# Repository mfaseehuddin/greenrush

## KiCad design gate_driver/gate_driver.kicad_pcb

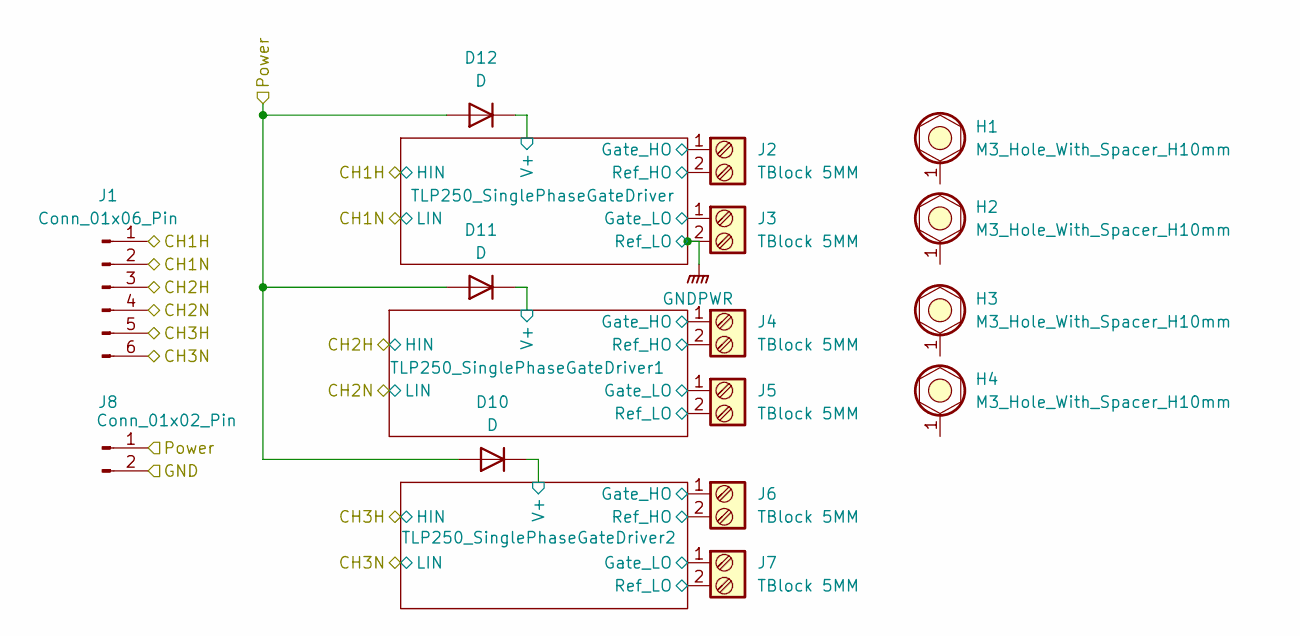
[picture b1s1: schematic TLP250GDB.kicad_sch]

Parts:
D10, D11, D12: D; D_5W_P10.16mm_Horizontal
H1, H2, H3, H4: M3_Hole_With_Spacer_H10mm; MountingHole_3.2mm_With_Spacer_H10mm
J1: Conn_01x06_Pin; PinHeader_1x06_P2.54mm_Vertical
J2, J3, J4, J5, J6, J7: TBlock 5MM; TerminalBlock_Phoenix_PT-1,5-2-5.0-H_1x02_P5.00mm_Horizontal
J8: Conn_01x02_Pin; PinHeader_1x02_P2.54mm_Vertical

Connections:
/Gate Driver Board/CH1H: J1.1; also elsewhere on the board
/Gate Driver Board/CH1N: J1.2; also elsewhere on the board
/Gate Driver Board/CH2H: J1.3; also elsewhere on the board
/Gate Driver Board/CH2N: J1.4; also elsewhere on the board
/Gate Driver Board/CH3H: J1.5; also elsewhere on the board
/Gate Driver Board/CH3N: J1.6; also elsewhere on the board
/Gate Driver Board/TLP250_SinglePhaseGateDriver1/Gate_HO: J4.1; also elsewhere on the board
/Gate Driver Board/TLP250_SinglePhaseGateDriver1/Gate_LO: J5.1; also elsewhere on the board
/Gate Driver Board/TLP250_SinglePhaseGateDriver1/Ref_HO: J4.2; also elsewhere on the board
/Gate Driver Board/TLP250_SinglePhaseGateDriver1/Ref_LO: J5.2; also elsewhere on the board
/Gate Driver Board/TLP250_SinglePhaseGateDriver1/V+: D11.1 (K); also elsewhere on the board
/Gate Driver Board/TLP250_SinglePhaseGateDriver2/Gate_HO: J6.1; also elsewhere on the board
/Gate Driver Board/TLP250_SinglePhaseGateDriver2/Gate_LO: J7.1; also elsewhere on the board
/Gate Driver Board/TLP250_SinglePhaseGateDriver2/Ref_HO: J6.2; also elsewhere on the board
/Gate Driver Board/TLP250_SinglePhaseGateDriver2/Ref_LO: J7.2; also elsewhere on the board
/Gate Driver Board/TLP250_SinglePhaseGateDriver2/V+: D10.1 (K); also elsewhere on the board
/Gate Driver Board/TLP250_SinglePhaseGateDriver/Gate_HO: J2.1; also elsewhere on the board
/Gate Driver Board/TLP250_SinglePhaseGateDriver/Gate_LO: J3.1; also elsewhere on the board
/Gate Driver Board/TLP250_SinglePhaseGateDriver/Ref_HO: J2.2; also elsewhere on the board
/Gate Driver Board/TLP250_SinglePhaseGateDriver/V+: D12.1 (K); also elsewhere on the board
GNDPWR: J3.2, J8.2; also elsewhere on the board
Vdrive: D10.2 (A), D11.2 (A), D12.2 (A), J8.1

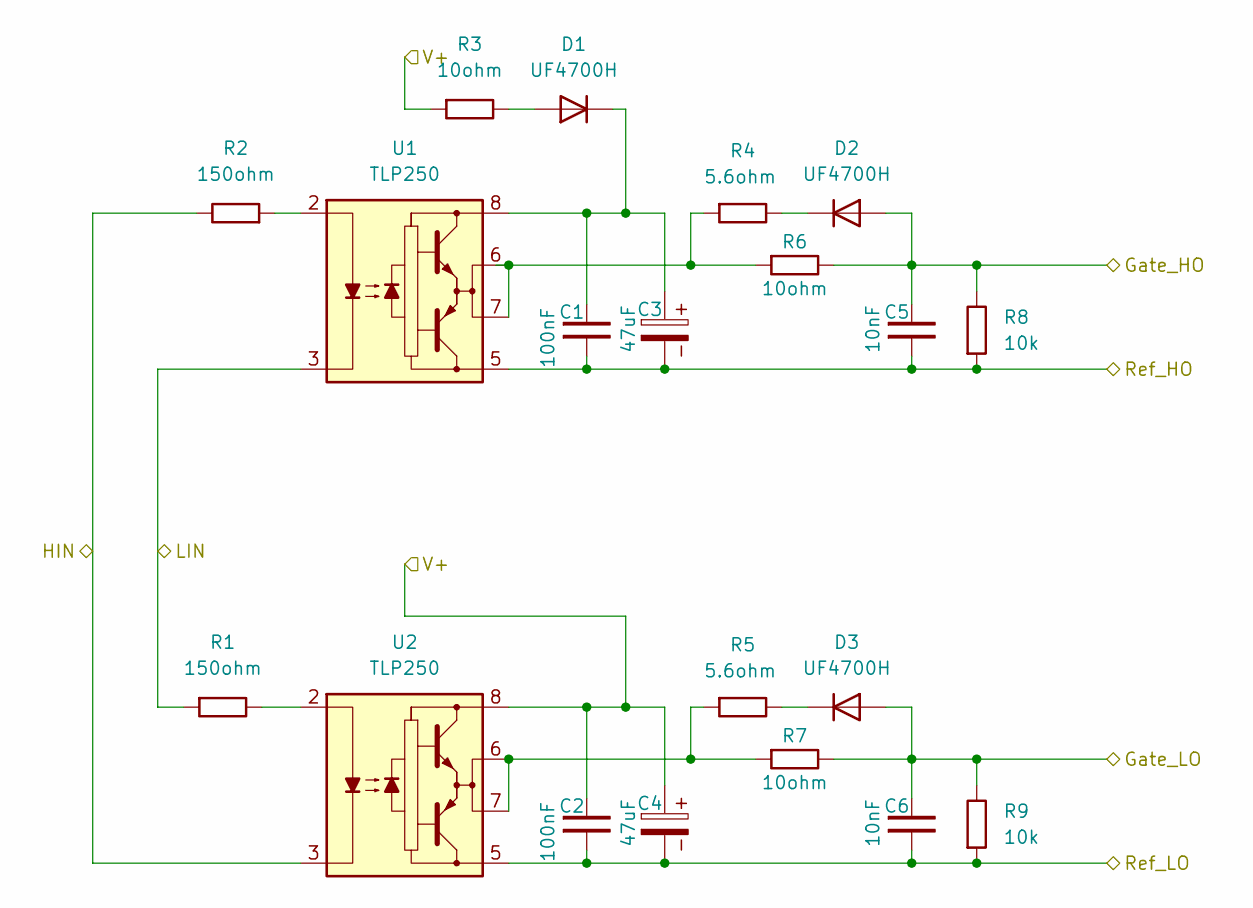
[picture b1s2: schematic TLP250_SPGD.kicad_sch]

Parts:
C1, C2: 100nF; C_Disc_D5.0mm_W2.5mm_P2.50mm
C3, C4: 47uF; C_Radial_D6.3mm_H11.0mm_P2.50mm
C5, C6: 10nF; C_Disc_D5.0mm_W2.5mm_P2.50mm
D1, D2, D3: UF4700H; D_A-405_P7.62mm_Horizontal
R1, R2: 150ohm; R_Axial_DIN0207_L6.3mm_D2.5mm_P7.62mm_Horizontal
R3, R6, R7: 10ohm; R_Axial_DIN0207_L6.3mm_D2.5mm_P7.62mm_Horizontal
R4, R5: 5.6ohm; R_Axial_DIN0207_L6.3mm_D2.5mm_P7.62mm_Horizontal
R8, R9: 10k; R_Axial_DIN0207_L6.3mm_D2.5mm_P7.62mm_Horizontal
U1, U2: TLP250; DIP-8_W7.62mm

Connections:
/Gate Driver Board/CH1H: R2.2, U2.3 (C); also elsewhere on the board
/Gate Driver Board/CH1N: R1.1, U1.3 (C); also elsewhere on the board
/Gate Driver Board/TLP250_SinglePhaseGateDriver/Gate_HO: C5.2, D2.2 (A), R6.2, R8.2; also elsewhere on the board
/Gate Driver Board/TLP250_SinglePhaseGateDriver/Gate_LO: C6.2, D3.2 (A), R7.2, R9.2; also elsewhere on the board
/Gate Driver Board/TLP250_SinglePhaseGateDriver/Ref_HO: C1.1, C3.2, C5.1, R8.1, U1.5 (VEE); also elsewhere on the board
/Gate Driver Board/TLP250_SinglePhaseGateDriver/V+: C2.2, C4.1, R3.1, U2.8 (VCC); also elsewhere on the board
GNDPWR: C2.1, C4.2, C6.1, R9.1, U2.5 (VEE); also elsewhere on the board
unnamed: D1.2 (A), R3.2
unnamed: C1.2, C3.1, D1.1 (K), U1.8 (VCC)
unnamed: D2.1 (K), R4.2
unnamed: D3.1 (K), R5.2
unnamed: R4.1, R6.1, U1.6 (VO), U1.7 (VO)
unnamed: R5.1, R7.1, U2.6 (VO), U2.7 (VO)
unnamed: R2.1, U1.2 (A)
unnamed: R1.2, U2.2 (A)

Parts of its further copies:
C7, C8, C13, C14: 100nF; C_Disc_D5.0mm_W2.5mm_P2.50mm
C9, C10, C15, C16: 47uF; C_Radial_D6.3mm_H11.0mm_P2.50mm
C11, C12, C17, C18: 10nF; C_Disc_D5.0mm_W2.5mm_P2.50mm
D4, D5, D6, D7, D8, D9: UF4700H; D_A-405_P7.62mm_Horizontal
R10, R11, R19, R20: 150ohm; R_Axial_DIN0207_L6.3mm_D2.5mm_P7.62mm_Horizontal
R12, R15, R16, R21, R24, R25: 10ohm; R_Axial_DIN0207_L6.3mm_D2.5mm_P7.62mm_Horizontal
R13, R14, R22, R23: 5.6ohm; R_Axial_DIN0207_L6.3mm_D2.5mm_P7.62mm_Horizontal
R17, R18, R26, R27: 10k; R_Axial_DIN0207_L6.3mm_D2.5mm_P7.62mm_Horizontal
U3, U4, U5, U6: TLP250; DIP-8_W7.62mm

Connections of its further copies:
/Gate Driver Board/CH2H: R11.2, U4.3 (C); also elsewhere on the board
/Gate Driver Board/CH2N: R10.1, U3.3 (C); also elsewhere on the board
/Gate Driver Board/CH3H: R20.2, U6.3 (C); also elsewhere on the board
/Gate Driver Board/CH3N: R19.1, U5.3 (C); also elsewhere on the board
/Gate Driver Board/TLP250_SinglePhaseGateDriver1/Gate_HO: C11.2, D5.2 (A), R15.2, R17.2; also elsewhere on the board
/Gate Driver Board/TLP250_SinglePhaseGateDriver1/Gate_LO: C12.2, D6.2 (A), R16.2, R18.2; also elsewhere on the board
/Gate Driver Board/TLP250_SinglePhaseGateDriver1/Ref_HO: C7.1, C9.2, C11.1, R17.1, U3.5 (VEE); also elsewhere on the board
/Gate Driver Board/TLP250_SinglePhaseGateDriver1/Ref_LO: C8.1, C10.2, C12.1, R18.1, U4.5 (VEE); also elsewhere on the board
/Gate Driver Board/TLP250_SinglePhaseGateDriver1/V+: C8.2, C10.1, R12.1, U4.8 (VCC); also elsewhere on the board
/Gate Driver Board/TLP250_SinglePhaseGateDriver2/Gate_HO: C17.2, D8.2 (A), R24.2, R26.2; also elsewhere on the board
/Gate Driver Board/TLP250_SinglePhaseGateDriver2/Gate_LO: C18.2, D9.2 (A), R25.2, R27.2; also elsewhere on the board
/Gate Driver Board/TLP250_SinglePhaseGateDriver2/Ref_HO: C13.1, C15.2, C17.1, R26.1, U5.5 (VEE); also elsewhere on the board
/Gate Driver Board/TLP250_SinglePhaseGateDriver2/Ref_LO: C14.1, C16.2, C18.1, R27.1, U6.5 (VEE); also elsewhere on the board
/Gate Driver Board/TLP250_SinglePhaseGateDriver2/V+: C14.2, C16.1, R21.1, U6.8 (VCC); also elsewhere on the board
unnamed: D4.2 (A), R12.2
unnamed: C7.2, C9.1, D4.1 (K), U3.8 (VCC)
unnamed: D5.1 (K), R13.2
unnamed: D6.1 (K), R14.2
unnamed: D7.2 (A), R21.2
unnamed: C13.2, C15.1, D7.1 (K), U5.8 (VCC)
unnamed: D8.1 (K), R22.2
unnamed: D9.1 (K), R23.2
unnamed: R13.1, R15.1, U3.6 (VO), U3.7 (VO)
unnamed: R14.1, R16.1, U4.6 (VO), U4.7 (VO)
unnamed: R22.1, R24.1, U5.6 (VO), U5.7 (VO)
unnamed: R23.1, R25.1, U6.6 (VO), U6.7 (VO)
unnamed: R11.1, U3.2 (A)
unnamed: R10.2, U4.2 (A)
unnamed: R20.1, U5.2 (A)
unnamed: R19.2, U6.2 (A)

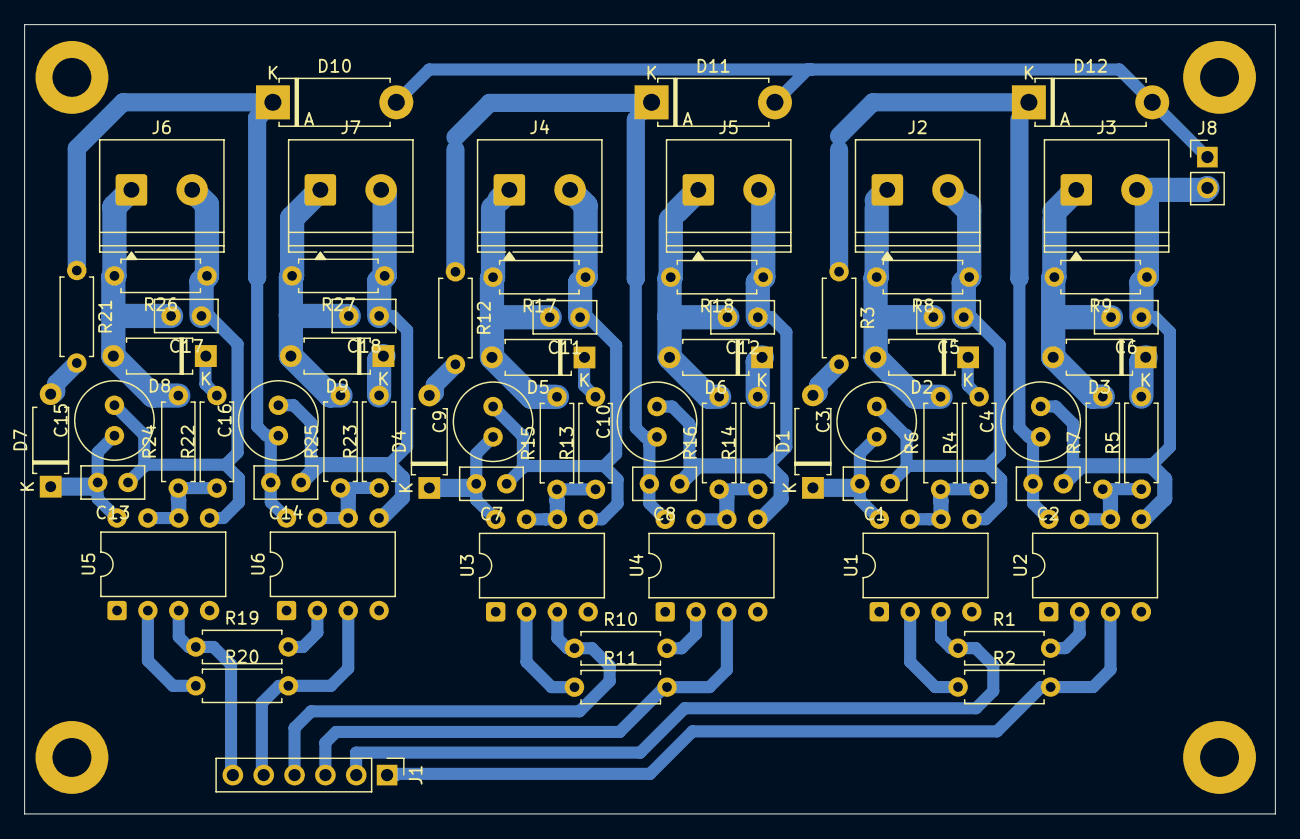
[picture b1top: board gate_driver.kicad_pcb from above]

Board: 2 copper layers, 103.0 x 65.0 mm, 75 parts (0 on the bottom side), 46 nets.

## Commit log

2025-04-27 This commit represnts the beginning of project mirgration to opensource platforms like KiCAD
